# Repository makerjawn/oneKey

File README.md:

jawnWare: oneKey (obsolete, check forked)
===========

Project Focus
-------------------
Developing a low-cost (<$2) and accessible derivative of the MaKey MaKey so that it can be sustainably deployed via workshops at various library branches. 

The aim is to introduce youth in underserved/low-income communities to making hardware that they can then tinker/play/make with. It's adressing the question "Can I take this home?" and the inability for youth to use take projects using digital media tools such as the MaKey MaKey home.

In participating in this process we hope for them to take more ownership of their tools. We're also trying to adress wether or not the library and its participants can make their own tools for learning via desktop manufacturing and production methods.

So what is a MaKey MaKey?
-------------------
From Sparkfun's [*MaKey MaKey Documentation*](https://github.com/sparkfun/makeymakey):

*"Using the MaKey MaKey you can make anything into a key (get it?) just by connecting a few alligator clips. The MaKey MaKey is an invention kit that tricks your computer into thinking that almost anything is a keyboard. This allows you to hook up all kinds of fun things as an input."*

**How does it work?**

*"The MaKey MaKey uses high resistance switching to detect when you've made a connection even through materials that aren't very conductive (like leaves, pasta or people). This technique attracts noise on the input, so a moving window averager is used to lowpass the noise. The on-board ATMega32u4 communicates with your computer using the Human Interface Device (HID) protocol which means that it can act like a keyboard or mouse."*

Methods
-------------------
The original oneKey uses a vinyl cutter and 3M copper tape to make a low-barrier and low-cost method for creating traces to solder onto. If working indoors take precautions with ventilalation etc. Working currently on a PCB kit version.

Need for the oneKey
-------------------
* 3M Copper Tape (used to be much cheaper, working on a thinner tape iteration.) ([Buy](http://www.amazon.com/inch-yds-Copper-Foil-Tape/dp/B00CBPM9RY/ref=sr_1_2?ie=UTF8&qid=1429671129&sr=8-2&keywords=copper+tape+3%22) | [HowTo](http://www.kobakant.at/DIY/?p=1132))
* Attiny85 ([Buy](http://www.digikey.com/product-detail/en/0/ATTINY85-20PU-ND) | [HowTo](about:blank))
* Attiny85 Standoff/ IC DIP Socket([Buy](http://www.digikey.com/product-detail/en/0/ATTINY85-20PU-ND) | [HowTo](about:blank))
* Resistors: 2x [68 ohm](http://www.digikey.com/product-detail/en/0/S68HCT-ND) , 1x [1.5K](http://www.digikey.com/product-detail/en/0/S1.5KHCT-ND), 1x [1M ohm](http://www.digikey.com/product-detail/en/0/CF14JT1M00CT-ND).
* Zener Diode ([Buy](http://www.digikey.com/product-detail/en/0/1N4148DICT-ND) | [HowTo](about:blank))
* USB Cable ([Buy](http://www.amazon.com/Eversame-Colorful-Hi-Speed-Universal-Phones-Black/dp/B00OC6WR22/ref=sr_1_1?s=pc&ie=UTF8&qid=1429671002&sr=1-1&keywords=10+pack+usb+cables) | [HowTo](about:blank))
* Vinyl Cutter (All makes/models work) ([Buy](http://www.amazon.com/Vinyl-Cutter-USCutter-34in-BUNDLE/dp/B00CDQGCTW/ref=sr_1_1?s=electronics&ie=UTF8&qid=1429671447&sr=1-1&keywords=vinyl+cutter) | [HowTo](about:blank))
* Soldering Iron ([Buy](about:blank) | [HowTo](about:blank))
* Needle Nose Pliers ([Buy](about:blank) | [HowTo](about:blank))
* Wire Cutter ([Buy](about:blank) | [HowTo](about:blank))
* Wire Stripper ([Buy](about:blank) | [HowTo](about:blank))
* Tiny AVR Programmer or Equivalent ([Buy](https://www.sparkfun.com/products/11801) | [HowTo](https://learn.sparkfun.com/tutorials/tiny-avr-programmer-hookup-guide/))

Repository Contents
-------------------
* **/Firmware** - Arduino Files+
* **/Hardware** - All design files (EAGLE, FRITIZING, AI+)
* **/Instructon** - Instructors materials
* **/Supplies** - Previous part orders

Variations
----------------
**Vinyl Cut Copper Tape** 

This build requres soldering and takes an hour to construct. The tape can be tricky to adhere to a substrate, but for all intents and purposes IT WORKS!

Requires the installation of the Digispark Arduino IDE to upload and run code from /Firmware.
All vector files needed for vinylcutting reside in /Hardware.

**PCB(REV.1)**  

Looking to make a PCB kit, currently waiting for PCB to be milled. See the Eagle Schematics and Board files in /Hardware.

**Quick-build(Still in Development)**  
This build is solderless, can be built in less than an hour.

Links/Sources
-------------------
* [Digispark](http://digistump.com/products/1)
* [Digispark IDE](about:blank)
* [Digispark Clone](about:blank)
* [BhavyaShukla - Makey-makey-using-arduino-uno-r3-Multiple-input](https://github.com/BhavyaShukla/Makey-makey-using-arduino-uno-r3-Multiple-inputs-)
* [Moving Avarage Library](https://github.com/BhavyaShukla/Makey-makey-using-arduino-uno-r3-Multiple-inputs-)
* [JoyLab's/Sparkfun's - MaKey MaKey](https://github.com/sparkfun/makeymakey)
* [avrdude tutorials](https://learn.adafruit.com/usbtinyisp/avrdude)

toDo
-------------------
* easier peeling
* solderless
* remove usb cable
* ~~thruhole prototype~~
* non-digispark
* attiny45?
* find other hardware thruhole prototype
* do outreach, find other ppl who want this

brief history
-------------------
To date two iterations of the one input MaKey MaKey derivative, "MaKey MaKey MaKey", or officially "oneKey" for short, have been deployed. The first generation proved that youth could make, hack, and play with their own hardware. After various form and material explorations as well as a circuit redesign it is currently in its second phase. The new design is easier to handle, the cost per unit has dropped from $7 to $1.30, it's quicker to make, and there is still much more to refine.

people
-------------------
* bk brandonklevence@gmail.com
* the Maker Jawn Initiative info@makerjawn.org

License Information
-------------------
The hardware is released under [Creative Commons Share-alike 3.0](http://creativecommons.org/licenses/by-sa/3.0/).  
All other code is open source hardware so please feel free to do anything you want with it; 
you buy me a beer if you use this and we meet someday ([Beerware license](http://en.wikipedia.org/wiki/Beerware)).
Please support [Digispark](https://github.com/sparkfun/makeymakey) and [JoyLabs](https://github.com/sparkfun/makeymakey) and buy their products if you decide to remix. Without their creativity and ingenuity this project would never have happened.

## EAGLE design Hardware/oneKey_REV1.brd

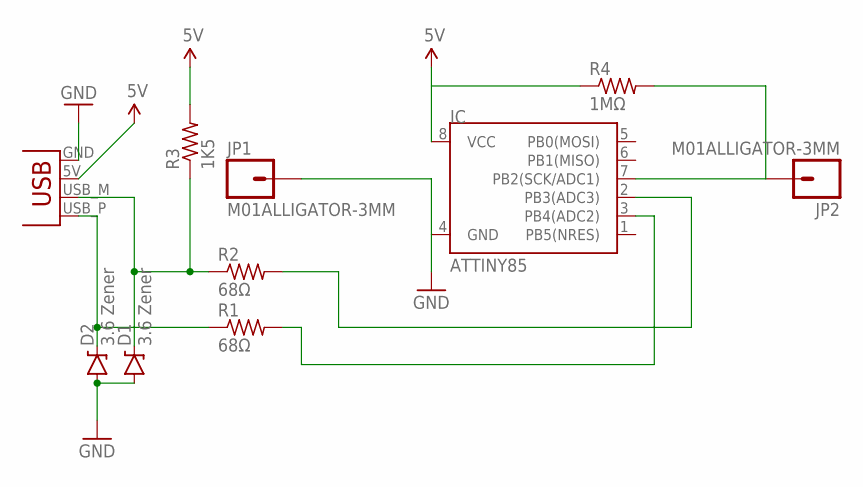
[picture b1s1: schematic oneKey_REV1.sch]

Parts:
D1, D2: 3.6 Zener; DIODE-ZENER
IC: ATTINY85; DIP08
JP1, JP2: M01ALLIGATOR-3MM; 1X01_ALLIGATOR_3MM
R1, R2: 68Ω; 0204/7
R3: 1K5; 0204/7
R4: 1MΩ; 0204/7
X1: USBPCB; USB-A-PCB

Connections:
5V: IC.8 (VCC), R3.2, R4.1, X1.5V (VBUS)
GND: D1.P$2 (A), D2.P$2 (A), IC.4 (GND), JP1.1@0, JP1.1@2, X1.GND
unnamed: IC.2 (PB3(ADC3)), R2.2
unnamed: IC.7 (PB2(SCK/ADC1)), JP2.1@0, JP2.1@2, R4.2
unnamed: IC.3 (PB4(ADC2)), R1.2
unnamed: D1.P$1 (C), R2.1, R3.1, X1.USB_M (D-)
unnamed: D2.P$1 (C), R1.1, X1.USB_P (D+)

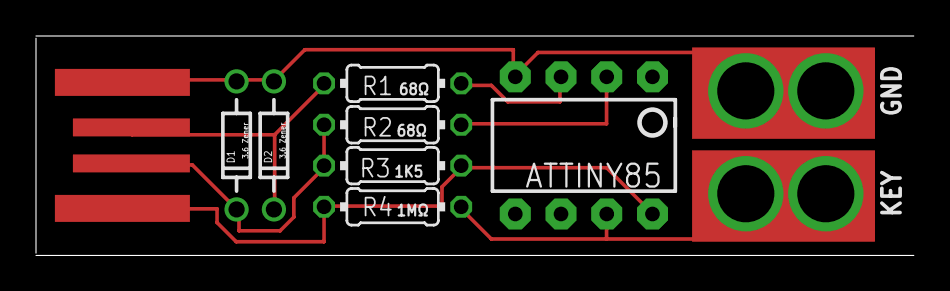
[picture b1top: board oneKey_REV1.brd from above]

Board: 2 copper layers, 48.8 x 12.2 mm, 11 parts (1 on the bottom side), 7 nets.

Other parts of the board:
U$4: OSHW-LOGO-S

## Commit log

2014-02-25 initial upload
2014-02-25 read me update
2014-02-25 readme_2
2014-02-25 rdme_3
2014-02-25 readme update
2014-02-25 readme
2014-04-28 cleaning house
2014-04-30 updating all the things
2014-04-30 failure in panama
2015-01-11 Restructure
    Documentation and Archive of iterations
2015-01-11 Organizing
    Documentation Updates, Archiving of Iterations, and much more. Will be
    updating readme soon.
2015-01-11 Instructors Materials
    See pdf
2015-03-15 update rm, eagle files, etc
2015-03-15 rdme
2015-03-15 lolo
2015-04-22 digikey order
2015-04-22 updated parts digikey buy links
2015-04-22 usb sample
    have found way cheaper lots in the past
2015-04-22 vinyl
2015-04-22 made proto

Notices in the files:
Hardware/oneKey_REV1.brd:
Design (schematic, layout, concept) is licensed under the Creative Commons Attribution-ShareAlike 3.0 Unported License: http://creativecommons.org/licenses/by-sa/3.0
parts and their libraries:
SparkFun: Licensing: CC v3.0 Share-Alike You are welcome to use this library for commercial purposes.
SparkFun-DiscreteSemi: Licensing: Creative Commons ShareAlike 4.0 International - https://creativecommons.org/licenses/by-sa/4.0
